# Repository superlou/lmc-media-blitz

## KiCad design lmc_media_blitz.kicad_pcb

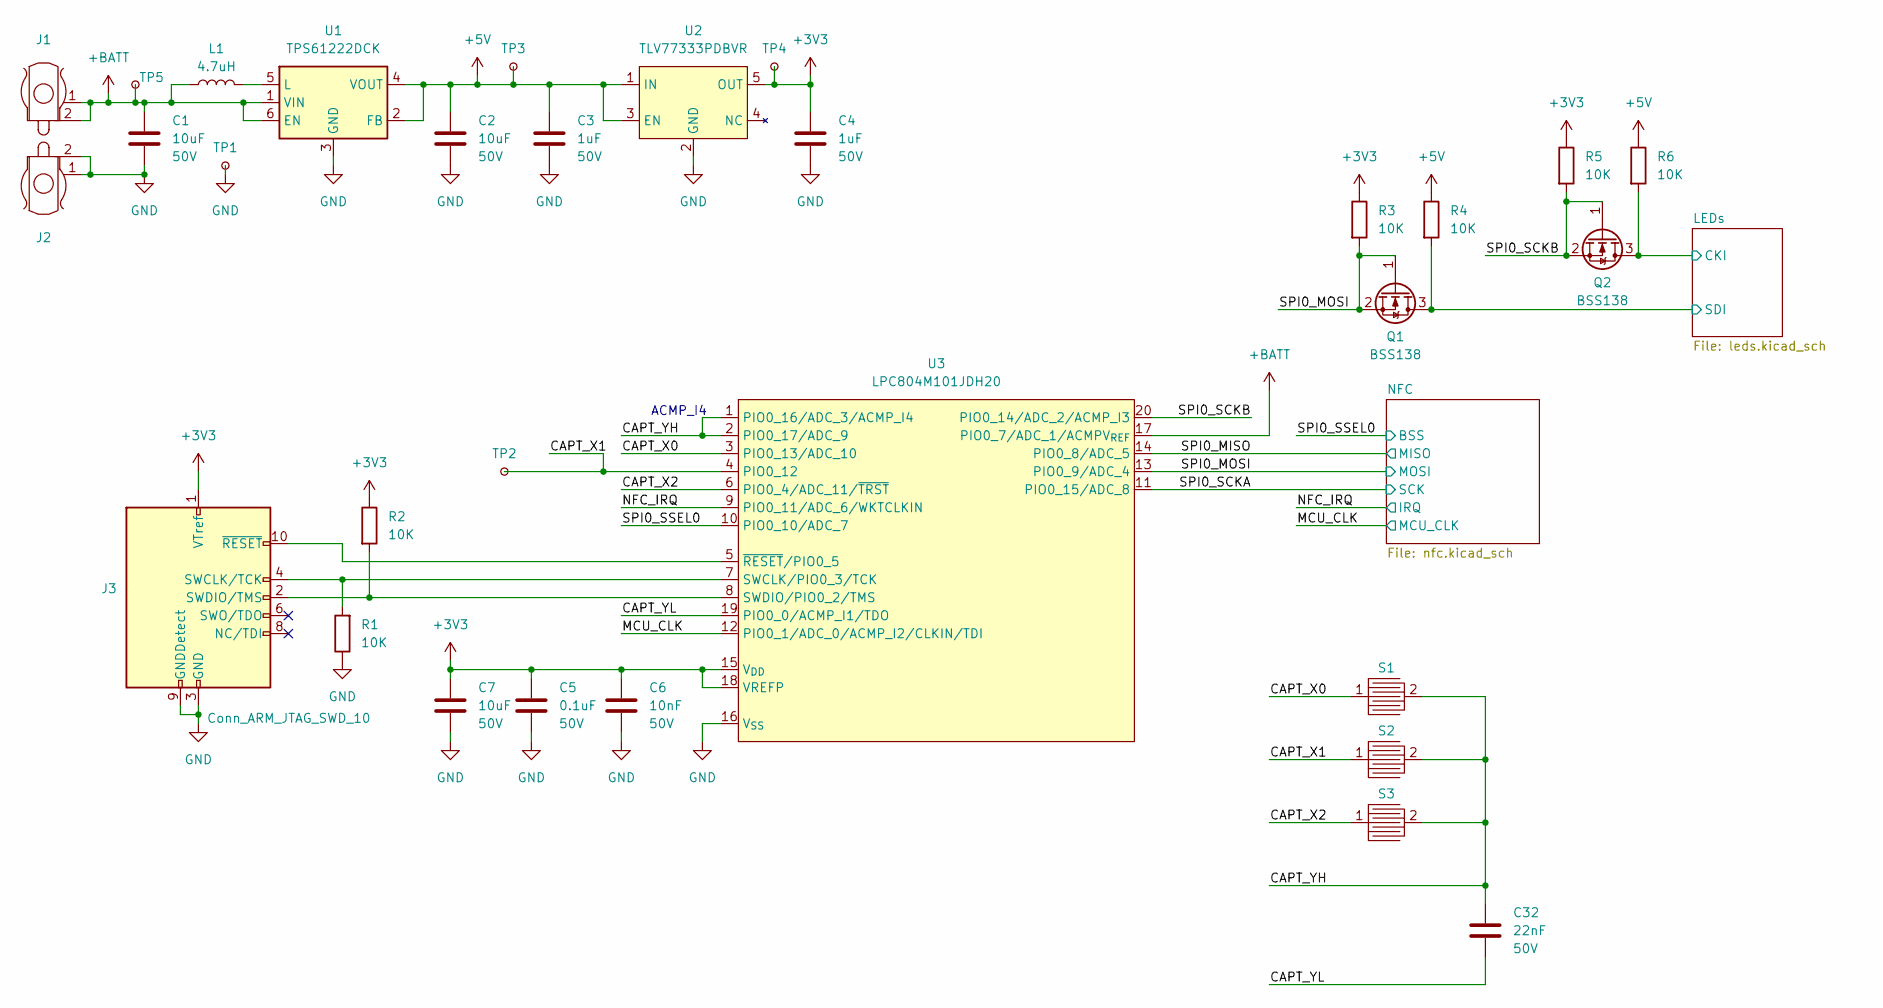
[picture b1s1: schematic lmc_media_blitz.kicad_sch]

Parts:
C1, C2, C7: 10uF; C_0805_2012Metric; Voltage 50V; LCSC Part # C440198
C3, C4: 1uF; C_0805_2012Metric; Voltage 50V; LCSC Part # C28323
C5: 0.1uF; C_0603_1608Metric; Voltage 50V; LCSC Part # C14663
C6: 10nF; C_0603_1608Metric; Voltage 50V; LCSC Part # C57112
C32: 22nF; C_0805_2012Metric; Voltage 50V; LCSC Part # C1729
J1, J2: Keystone82
J3: Conn_ARM_JTAG_SWD_10; PinHeader_2x05_P1.27mm_Vertical_SMD; LCSC Part # C5296739
L1: 4.7uH; L_Taiyo-Yuden_MD-3030; LCSC Part # C87172
Q1, Q2: BSS138; SOT-23; LCSC Part # C78284
R1, R2, R3, R4, R5, R6: 10K; R_0805_2012Metric; LCSC Part # C17414
S1, S2, S3: CapTouchButton
TP1, TP2, TP3, TP4, TP5: TestPoint_Small; TestPoint_Pad_D2.0mm
U1: TPS61222DCK; Texas_R-PDSO-G6; LCSC Part # C116461
U2: TLV77333PDBVR; SOT-23-5; LCSC Part # C134139
U3: LPC804M101JDH20; TSSOP-20_4.4x6.5mm_P0.65mm; LCSC Part # C2056857

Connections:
+3V3: C4.1, C5.1, C6.1, C7.2, J3.1 (VTref), R2.1, R3.1, R5.1, TP4.1, U2.5 (OUT), U3.15 (V_{DD}), U3.18 (VREFP); also elsewhere on the board
+5V: C2.2, C3.1, R4.1, R6.1, TP3.1, U1.2 (FB), U1.4 (VOUT), U2.1 (IN), U2.3 (EN); also elsewhere on the board
+BATT: C1.2, J1.1, J1.2, L1.1, TP5.1, U1.1 (VIN), U1.6 (EN), U3.17 (PIO0_7/ADC_1/ACMPV_{REF})
/CAPT_X0: S1.1, U3.3 (PIO0_13/ADC_10)
/CAPT_X1: S2.1, TP2.1, U3.4 (PIO0_12)
/CAPT_X2: S3.1, U3.6 (PIO0_4/ADC_11/~TRST)
/CAPT_YH: C32.1, S1.2, S2.2, S3.2, U3.1 (PIO0_16/ADC_3/ACMP_I4), U3.2 (PIO0_17/ADC_9)
/CAPT_YL: C32.2, U3.19 (PIO0_0/ACMP_I1/TDO)
/LEDs/CKI: Q2.3 (D), R6.2; also elsewhere on the board
/LEDs/SDI: Q1.3 (D), R4.2; also elsewhere on the board
/MCU_CLK: U3.12 (PIO0_1/ADC_0/ACMP_I2/CLKIN/TDI); also elsewhere on the board
/NFC_IRQ: U3.9 (PIO0_11/ADC_6/WKTCLKIN); also elsewhere on the board
/SPI0_MISO: U3.14 (PIO0_8/ADC_5); also elsewhere on the board
/SPI0_MOSI: Q1.1 (G), Q1.2 (S), R3.2, U3.13 (PIO0_9/ADC_4); also elsewhere on the board
/SPI0_SCKA: U3.11 (PIO0_15/ADC_8); also elsewhere on the board
/SPI0_SCKB: Q2.1 (G), Q2.2 (S), R5.2, U3.20 (PIO0_14/ADC_2/ACMP_I3)
/SPI0_SSEL0: U3.10 (PIO0_10/ADC_7); also elsewhere on the board
GND: C1.1, C2.1, C3.2, C4.2, C5.2, C6.2, C7.1, J2.1, J2.2, J3.3 (GND), J3.5 (GND), J3.9 (GNDDetect), R1.1, TP1.1, U1.3 (GND), U2.2 (GND), U3.16 (V_{SS}); also elsewhere on the board
unnamed: J3.4 (SWCLK/TCK), R1.2, U3.7 (SWCLK/PIO0_3/TCK)
unnamed: J3.2 (SWDIO/TMS), R2.2, U3.8 (SWDIO/PIO0_2/TMS)
unnamed: J3.10 (~RESET), U3.5 (~RESET/PIO0_5)
unnamed: L1.2, U1.5 (L)

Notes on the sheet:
ACMP_I4

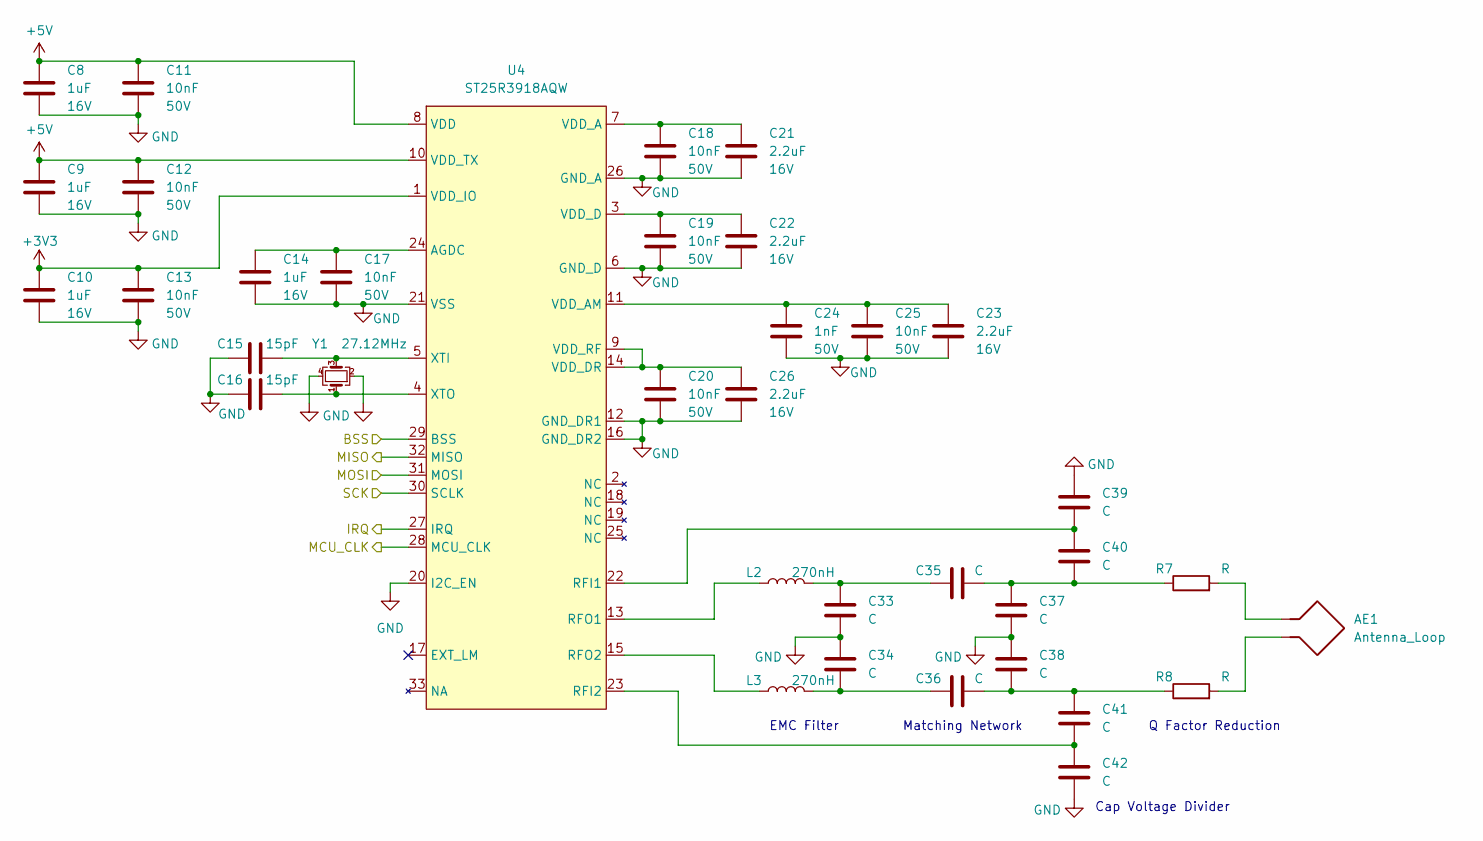
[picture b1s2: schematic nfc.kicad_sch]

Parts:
AE1: Antenna_Loop; badge_antenna
C8, C9, C10, C14: 1uF; C_0603_1608Metric; Voltage 16V; LCSC Part # C15849
C11, C12, C13, C17, C18, C19, C20, C25: 10nF; C_0603_1608Metric; Voltage 50V; LCSC Part # C57112
C15, C16: 15pF; C_0603_1608Metric; LCSC Part # C1644
C21, C22, C23, C26: 2.2uF; C_0603_1608Metric; Voltage 16V; LCSC Part # C23630
C24: 1nF; C_0603_1608Metric; Voltage 50V; LCSC Part # C1588
C33, C34, C35, C36, C37, C38, C39, C40, C41, C42: C; C_0805_2012Metric
L2, L3: 270nH; L_0805_2012Metric; LCSC Part # C107522
R7, R8: R; R_0805_2012Metric
U4: ST25R3918AQW; HVQFN-32-1EP_5x5mm_P0.5mm_EP3.1x3.1mm; LCSC Part # C3304617
Y1: 27.12MHz; Crystal_SMD_Abracon_ABM8G-4Pin_3.2x2.5mm; LCSC Part # C70591

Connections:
+3V3: C10.1, C13.1, U4.1 (VDD_IO); also elsewhere on the board
+5V: C8.1, C9.1, C11.1, C12.1, U4.8 (VDD), U4.10 (VDD_TX); also elsewhere on the board
/MCU_CLK: U4.28 (MCU_CLK); also elsewhere on the board
/NFC_IRQ: U4.27 (IRQ); also elsewhere on the board
/SPI0_MISO: U4.32 (MISO); also elsewhere on the board
/SPI0_MOSI: U4.31 (MOSI); also elsewhere on the board
/SPI0_SCKA: U4.30 (SCLK); also elsewhere on the board
/SPI0_SSEL0: U4.29 (BSS); also elsewhere on the board
GND: C8.2, C9.2, C10.2, C11.2, C12.2, C13.2, C14.2, C15.2, C16.2, C17.2, C18.2, C19.2, C20.2, C21.1, C22.1, C23.1, C24.2, C25.2, C26.1, C33.2, C34.1, C37.2, C38.1, C39.1, C42.2, U4.6 (GND_D), U4.12 (GND_DR1), U4.16 (GND_DR2), U4.20 (I2C_EN), U4.21 (VSS), U4.26 (GND_A), Y1.2, Y1.4; also elsewhere on the board
unnamed: AE1.1, R7.2
unnamed: AE1.2, R8.2
unnamed: C33.1, C35.1, L2.2
unnamed: C34.2, C36.1, L3.2
unnamed: C35.2, C37.1, C40.2, R7.1
unnamed: C36.2, C38.2, C41.1, R8.1
unnamed: C14.1, C17.1, U4.24 (AGDC)
unnamed: C39.2, C40.1, U4.22 (RFI1)
unnamed: C41.2, C42.1, U4.23 (RFI2)
unnamed: L2.1, U4.13 (RFO1)
unnamed: L3.1, U4.15 (RFO2)
unnamed: C18.1, C21.2, U4.7 (VDD_A)
unnamed: C23.2, C24.1, C25.1, U4.11 (VDD_AM)
unnamed: C19.1, C22.2, U4.3 (VDD_D)
unnamed: C20.1, C26.2, U4.9 (VDD_RF), U4.14 (VDD_DR)
unnamed: C15.1, U4.5 (XTI), Y1.3
unnamed: C16.1, U4.4 (XTO), Y1.1

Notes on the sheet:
Q Factor Reduction
EMC Filter
Cap Voltage Divider
Matching Network

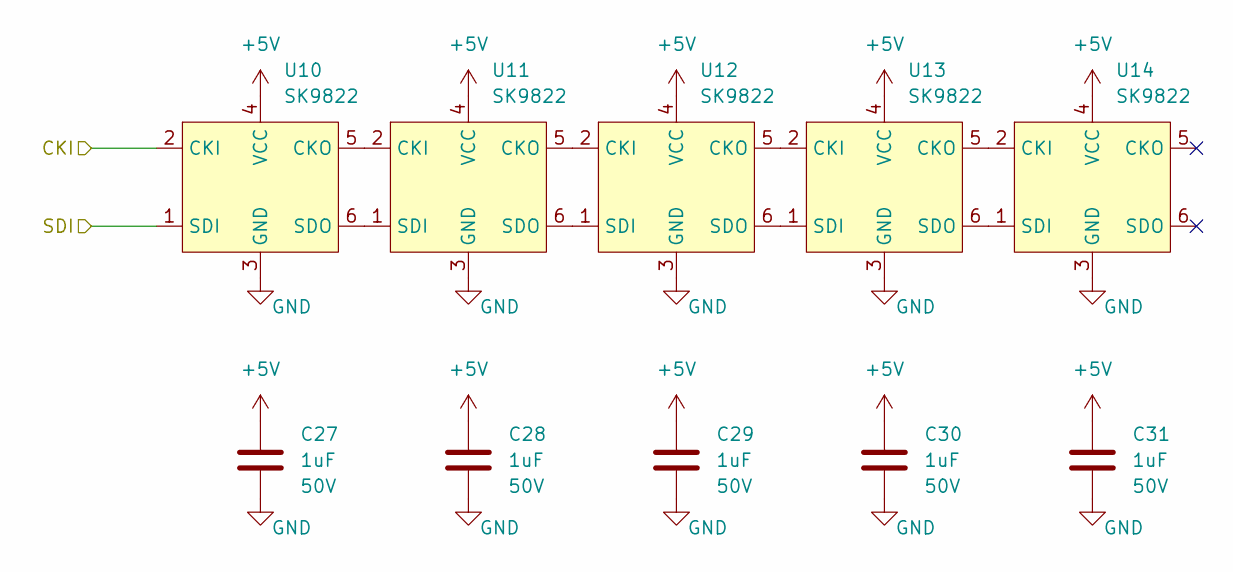
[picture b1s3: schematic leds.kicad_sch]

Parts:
C27, C28, C29, C30, C31: 1uF; C_0805_2012Metric; Voltage 50V; LCSC Part # C28323
U10, U11, U12, U13, U14: SK9822; OPSCO_SK9822; LCSC Part # C5378730

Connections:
+5V: C27.1, C28.1, C29.1, C30.1, C31.1, U10.4 (VCC), U11.4 (VCC), U12.4 (VCC), U13.4 (VCC), U14.4 (VCC); also elsewhere on the board
/LEDs/CKI: U10.2 (CKI); also elsewhere on the board
/LEDs/SDI: U10.1 (SDI); also elsewhere on the board
GND: C27.2, C28.2, C29.2, C30.2, C31.2, U10.3 (GND), U11.3 (GND), U12.3 (GND), U13.3 (GND), U14.3 (GND); also elsewhere on the board
unnamed: U10.5 (CKO), U11.2 (CKI)
unnamed: U10.6 (SDO), U11.1 (SDI)
unnamed: U11.5 (CKO), U12.2 (CKI)
unnamed: U11.6 (SDO), U12.1 (SDI)
unnamed: U12.5 (CKO), U13.2 (CKI)
unnamed: U12.6 (SDO), U13.1 (SDI)
unnamed: U13.5 (CKO), U14.2 (CKI)
unnamed: U13.6 (SDO), U14.1 (SDI)

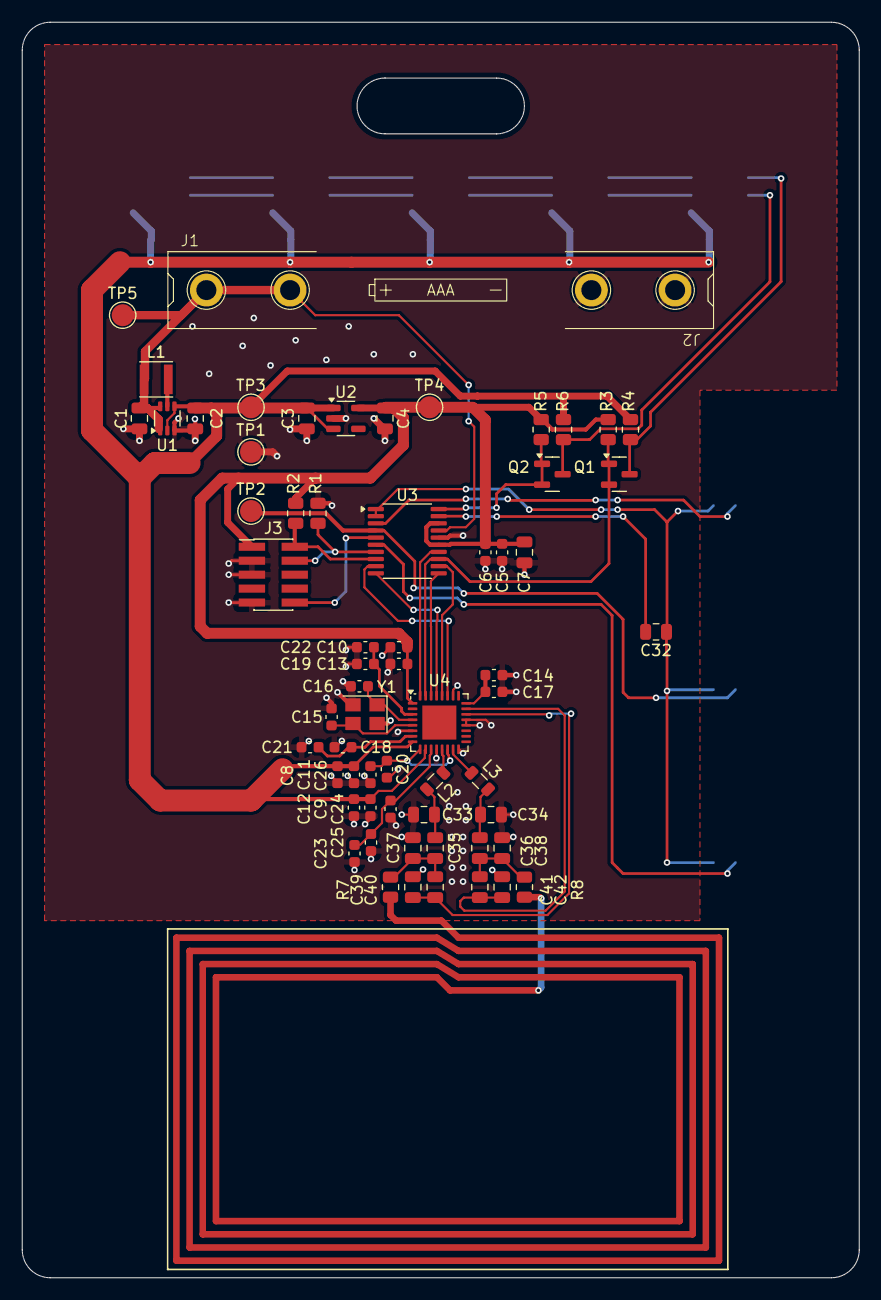
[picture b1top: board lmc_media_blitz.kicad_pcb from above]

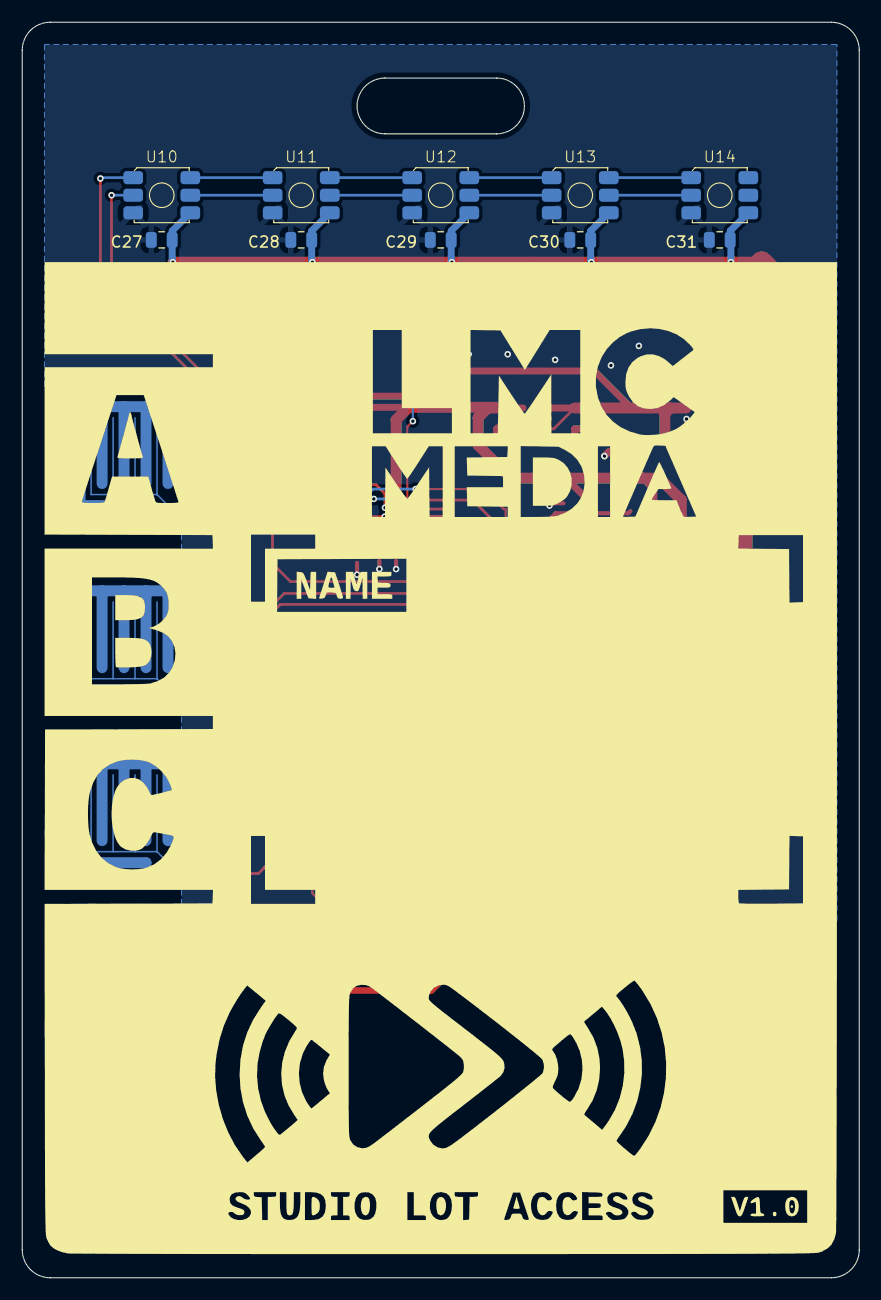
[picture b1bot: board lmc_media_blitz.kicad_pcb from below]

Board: 2 copper layers, 76.2 x 114.3 mm, 77 parts (13 on the bottom side), 47 nets.

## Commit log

2025-01-29 Added some footprints and cap touch symbols
2025-01-31 Adding some stuf
2025-02-03 Initial routing
2025-02-03 Fixed most DRC errors, but need to relayout RFO/RFI
2025-02-03 More silk fixes
2025-02-04 Relayout NFC output
2025-02-05 Added more
2025-02-06 Optimizing components for ordering
2025-02-23 Converted to Kicad 9
